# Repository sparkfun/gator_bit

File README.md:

SparkFun gator:bit v2
========================================

[*SparkFun gator:bit v2 (15162)*](https://www.sparkfun.com/products/15162)

The SparkFun gator:bit is an all-in-one prototyping platform for the micro:bit. Each pin is accessible by alligator clip, eliminating the need for breadboard or jumper wires.

Repository Contents
------------------
* **/Firmware** - Example code used with gator:bit. While they are compiled HEX codes, you can modify the example code once they are imported into MakeCode editor.
* **/Hardware** - Eagle design files (.brd, .sch)
* **/Production** - Production panel files (.brd)

Documentation
--------------
* **[Hookup Guide](https://learn.sparkfun.com/tutorials/sparkfun-gatorbit-v20-hookup-guide)** - Basic hookup guide for the gator:bit v2.

Versions
--------------
* **[v1](https://github.com/sparkfun/gator_bit/tree/v10)** - Version 1, Initial Release
* **[v2](https://github.com/sparkfun/gator_bit/)** - Version 2, Updated power handling, output pins now reach a proper voltage.

License Information
-------------------

This product is _**open source**_! 

Please review the LICENSE.md file for license information. 

If you have any questions or concerns on licensing, please contact techsupport@sparkfun.com.

Distributed as-is; no warranty is given.

- Your friends at SparkFun.

_<COLLABORATION CREDIT>_

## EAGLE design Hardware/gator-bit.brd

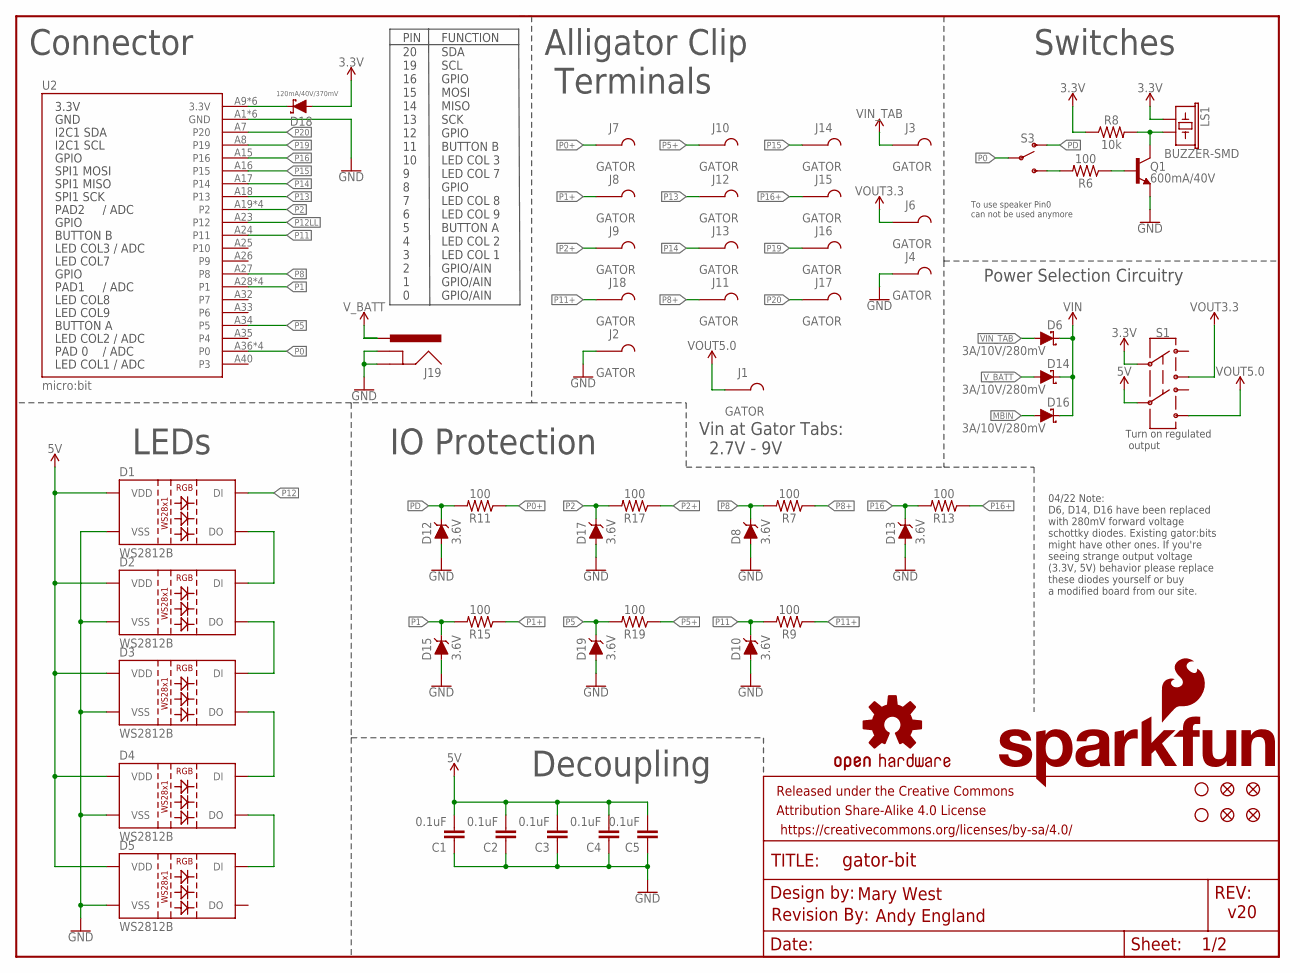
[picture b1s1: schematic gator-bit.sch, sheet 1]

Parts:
C1, C2, C3, C4, C5: 0.1uF; 0603
D1, D2, D3, D4, D5: WS2812B
D6, D14, D16: 3A/10V/280mV; SOD-323
D8, D10, D12, D13, D15, D17, D19: 3.6V; SOD-323
D18: 120mA/40V/370mV; SOD-523
FD1, FD2, FD3, FD4: FIDUCIAL1X2; FIDUCIAL-1X2
FRAME1: FRAME-LETTER; CREATIVE_COMMONS
H1, H2: STAND-OFF
J1, J2, J3, J4, J6, J7, J8, J9, J10, J11, J12, J13, J14, J15, J16, J17, J18: GATOR
J19: POWER_JACKPTH_LOCK; POWER_JACK_PTH_LOCK
LOGO1: SFE_LOGO_NAME_FLAME.3_INCH; SFE_LOGO_NAME_FLAME_.3
LOGO2: OSHW-LOGOM; OSHW-LOGO-M
LOGO3: REVISION
LS1: BUZZER-SMD; BUZZER-CCV
Q1: 600mA/40V; SOT23-3
R6, R7, R9, R11, R13, R15, R17, R19: 100; 0603
R8: 10k; 0603
S1: SWITCH-DPDT-SMD-AYZ0202; SWITCH_DPDT_SMD_AYZ0202
S3: SWITCH-SPDT-SMD-AYZ0202; SWITCH_DPDT_SMD_AYZ0202
U2: micro:bit; MICRO:BIT_RA_PTH

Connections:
3.3V: D18.A, LS1.+ (1), R8.1, S1.2; also elsewhere on the board
5V: C1.2, C2.2, C3.2, C4.2, C5.2, D1.1 (VDD), D2.1 (VDD), D3.1 (VDD), D4.1 (VDD), D5.1 (VDD), S1.5; also elsewhere on the board
GND: C1.1, C2.1, C3.1, C4.1, C5.1, D1.3 (VSS), D2.3 (VSS), D3.3 (VSS), D4.3 (VSS), D5.3 (VSS), D8.A, D10.A, D12.A, D13.A, D15.A, D17.A, D19.A, J2.P$1, J2.P$2, J4.P$1, J4.P$2, J19.GND, J19.GNDBREAK, Q1.2 (E), U2.A1 (GND), U2.A2 (GND), U2.A3 (GND), U2.A4 (GND), U2.A5 (GND), U2.A6 (GND); also elsewhere on the board
MBIN: D16.A, D18.C, U2.A9 (3.3V), U2.A10 (3.3V), U2.A11 (3.3V), U2.A12 (3.3V), U2.A13 (3.3V), U2.A14 (3.3V)
unnamed: LS1.- (2), Q1.3 (C), R8.2
unnamed: D1.2 (DO), D2.4 (DI)
unnamed: D2.2 (DO), D3.4 (DI)
unnamed: D3.2 (DO), D4.4 (DI)
unnamed: D4.2 (DO), D5.4 (DI)
unnamed: R6.2, S3.3 (S)
unnamed: Q1.1 (B), R6.1
P0: S3.2, U2.A36 (P0), U2.A37 (P0), U2.A38 (P0), U2.A39 (P0)
P0+: J7.P$1, J7.P$2, R11.1
P1: D15.C, R15.2, U2.A28 (P1), U2.A29 (P1), U2.A30 (P1), U2.A31 (P1)
P1+: J8.P$1, J8.P$2, R15.1
P2: D17.C, R17.2, U2.A19 (P2), U2.A20 (P2), U2.A21 (P2), U2.A22 (P2)
P2+: J9.P$1, J9.P$2, R17.1
P5: D19.C, R19.2, U2.A34 (P5)
P5+: J10.P$1, J10.P$2, R19.1
P8: D8.C, R7.2, U2.A27 (P8)
P8+: J11.P$1, J11.P$2, R7.1
P11: D10.C, R9.2, U2.A24 (P11)
P11+: J18.P$1, J18.P$2, R9.1
P12: D1.4 (DI); also elsewhere on the board
P12LL: U2.A23 (P12); also elsewhere on the board
P13: J12.P$1, J12.P$2, U2.A18 (P13)
P14: J13.P$1, J13.P$2, U2.A17 (P14)
P15: J14.P$1, J14.P$2, U2.A16 (P15)
P16: D13.C, R13.2, U2.A15 (P16)
P16+: J15.P$1, J15.P$2, R13.1
P19: J16.P$1, J16.P$2, U2.A8 (P19)
P20: J17.P$1, J17.P$2, U2.A7 (P20)
PD: D12.C, R11.2, S3.1 (O)
VIN: D6.C, D14.C, D16.C; also elsewhere on the board
VIN_TAB: D6.A, J3.P$1, J3.P$2
VOUT3.3: J6.P$1, J6.P$2, S1.3; also elsewhere on the board
VOUT5.0: J1.P$1, J1.P$2, S1.6; also elsewhere on the board
V_BATT: D14.A, J19.PWR

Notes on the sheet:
v20
Connector
20 19 16 15 14 13 12 11 10 9 8 7 6 5 4 3 2 1 0
SDA SCL GPIO MOSI MISO SCK GPIO BUTTON B LED COL 3 LED COL 7 GPIO LED COL 8 LED COL 9 BUTTON A LED COL 2 LED COL 1 GPIO/AIN GPIO/AIN GPIO/AIN
PIN
FUNCTION
Mary West
Alligator Clip Terminals
Switches
LEDs
Decoupling
IO Protection
To use speaker Pin0 can not be used anymore
Power Selection Circuitry
Turn on regulated output
Vin at Gator Tabs: 2.7V - 9V
Andy England
04/22 Note: D6, D14, D16 have been replaced with 280mV forward voltage schottky diodes. Existing gator:bits might have other ones. If you're seeing strange output voltage (3.3V, 5V) behavior please replace these diodes yourself or buy a modified board from our site.

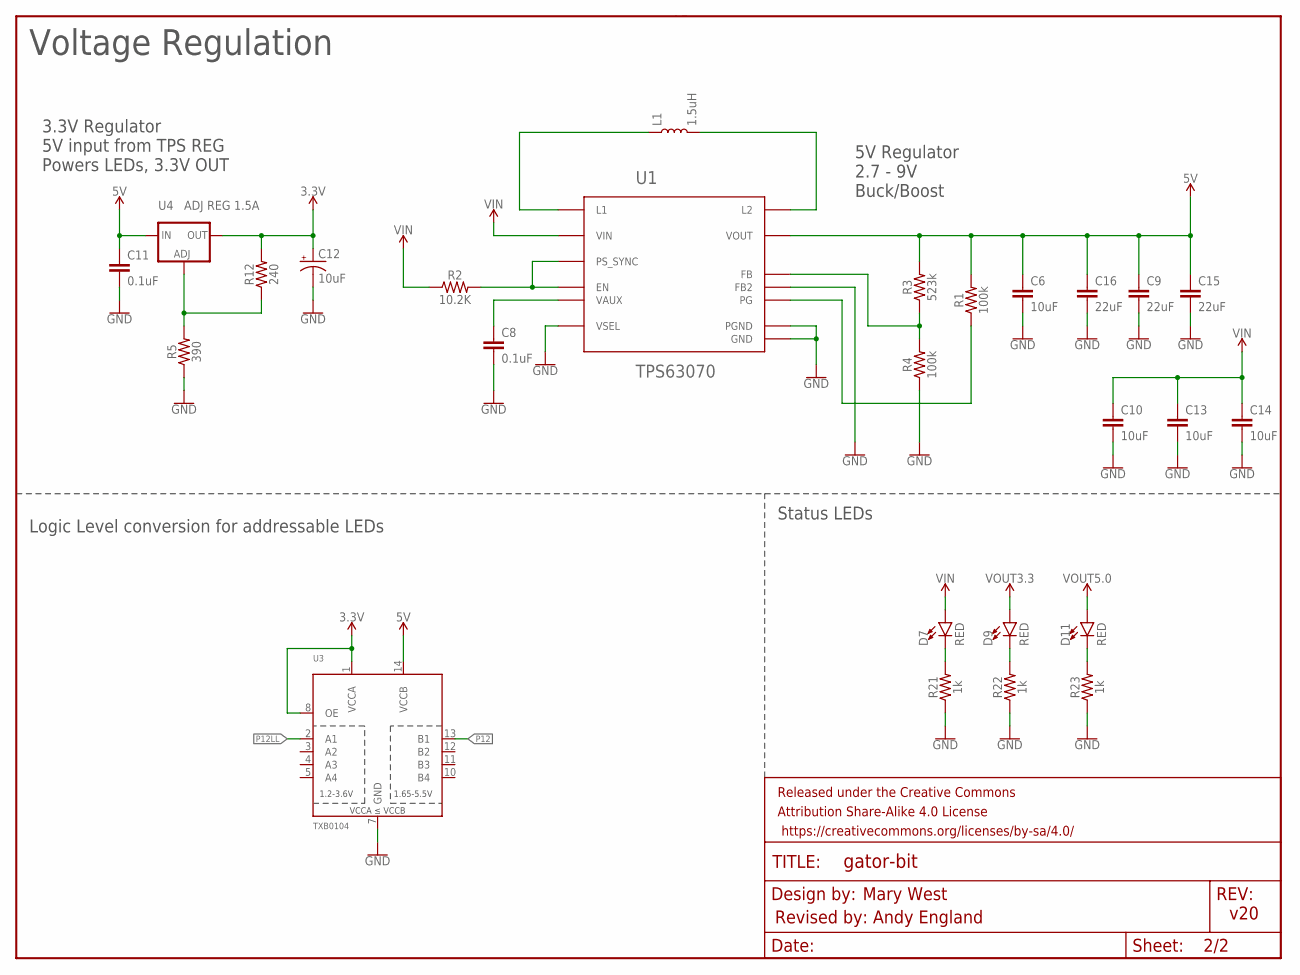
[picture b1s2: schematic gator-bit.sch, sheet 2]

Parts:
C6, C14: 10uF; 0603
C8, C11: 0.1uF; 0603
C9, C15, C16: 22uF; 0805
C10, C13: 10uF; 0805
C12: 10uF; EIA3216
D7, D9, D11: RED; LED-0603
FRAME3: FRAME-LETTER; CREATIVE_COMMONS
L1: 1.5uH; XFL4020
R1, R4: 100k; 0603
R2: 10.2K; 0603
R3: 523k; 0603
R5: 390; 0603
R12: 240; 0603
R21, R22, R23: 1k; 0603
U1: TPS63070; TPS63070RNM
U3: TXB0104; TSSOP14
U4: ADJ REG 1.5A; SOT223

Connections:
3.3V: C12.+, R12.2, U3.1 (VCCA), U3.8 (OE), U4.2 (OUT), U4.4 (OUT); also elsewhere on the board
5V: C6.1, C9.1, C11.1, C15.1, C16.1, R1.2, R3.2, U1.P$7 (VOUT), U3.14 (VCCB), U4.3 (IN); also elsewhere on the board
GND: C6.2, C8.2, C9.2, C10.2, C11.2, C12.-, C13.2, C14.2, C15.2, C16.2, R4.1, R5.1, R21.1, R22.1, R23.1, U1.P$4 (GND), U1.P$6 (FB2), U1.P$10 (PGND), U1.P$15 (VSEL), U3.7 (GND); also elsewhere on the board
unnamed: L1.P$1 (1), U1.P$11 (L1)
unnamed: L1.P$2 (2), U1.P$9 (L2)
unnamed: D7.C, R21.2
unnamed: R3.1, R4.2, U1.P$5 (FB)
unnamed: C8.1, U1.P$3 (VAUX)
unnamed: R2.2, U1.P$1 (PS_SYNC), U1.P$14 (EN)
unnamed: R1.1, U1.P$2 (PG)
unnamed: R5.2, R12.1, U4.1 (ADJ)
unnamed: D9.C, R22.2
unnamed: D11.C, R23.2
P12: U3.13 (B1); also elsewhere on the board
P12LL: U3.2 (A1); also elsewhere on the board
VIN: C10.1, C13.1, C14.1, D7.A, R2.1, U1.P$12 (VIN); also elsewhere on the board
VOUT3.3: D9.A; also elsewhere on the board
VOUT5.0: D11.A; also elsewhere on the board

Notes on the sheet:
Voltage Regulation
Mary West
v20
5V Regulator 2.7 - 9V Buck/Boost
3.3V Regulator 5V input from TPS REG Powers LEDs, 3.3V OUT
Logic Level conversion for addressable LEDs
Status LEDs
Revised by: Andy England

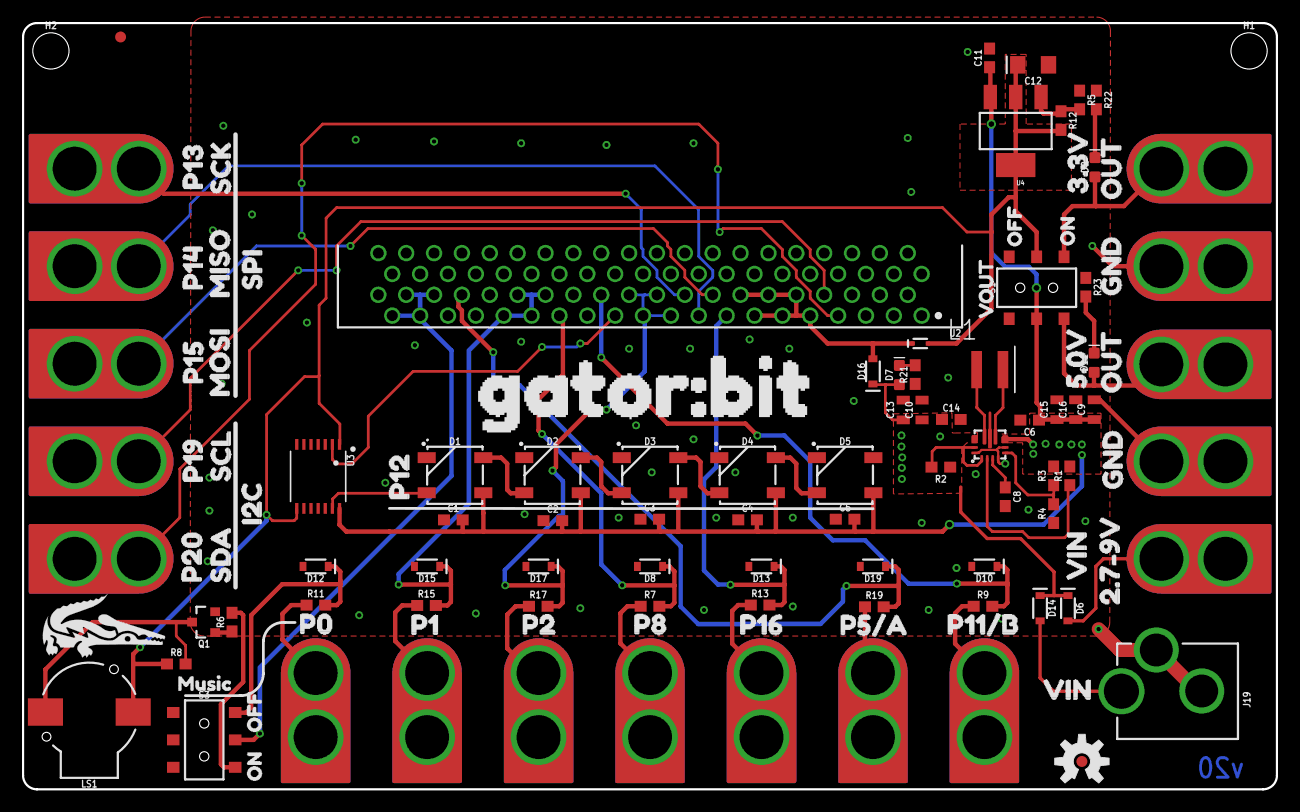
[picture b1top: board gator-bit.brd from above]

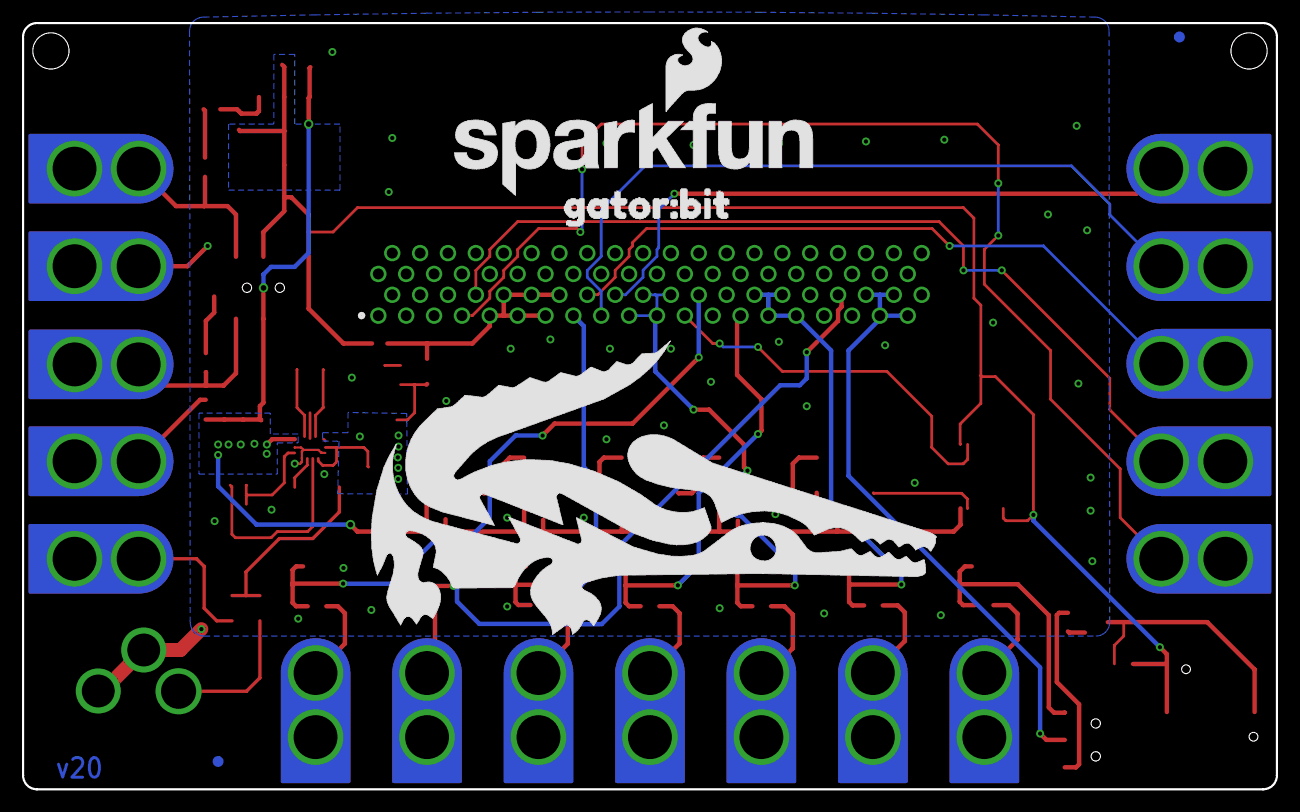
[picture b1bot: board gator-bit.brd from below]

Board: 2 copper layers, 114.3 x 69.8 mm, 128 parts (4 on the bottom side), 48 nets.

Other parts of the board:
U$1: 2#7#9V21
U$2: 3#3V25
U$3: 5#0V23
U$4: ORDERING_INSTRUCTIONS
U$5: GATOR#BIT26
U$6: GATOR#BIT32
U$7, U$8: GND22
U$9: I2C7
U$10: MISO5
U$11: MOSI4
U$12: MUSIC28
U$13, U$36: OFF29
U$14, U$37: ON30
U$15, U$16: OUT24
U$17: P5#A18
U$18: P11#B19
U$19: P013
U$20: P114
U$21: P130
U$22: P199
U$23: P208
U$24: P215
U$25: P816
U$26: P1227
U$27: P1411
U$28: P1510
U$29: P1617
U$30: SCK1
U$31: SCL2
U$32: SDA3
U$33: SPI6
U$34, U$39: VIN20
U$35: VOUT31

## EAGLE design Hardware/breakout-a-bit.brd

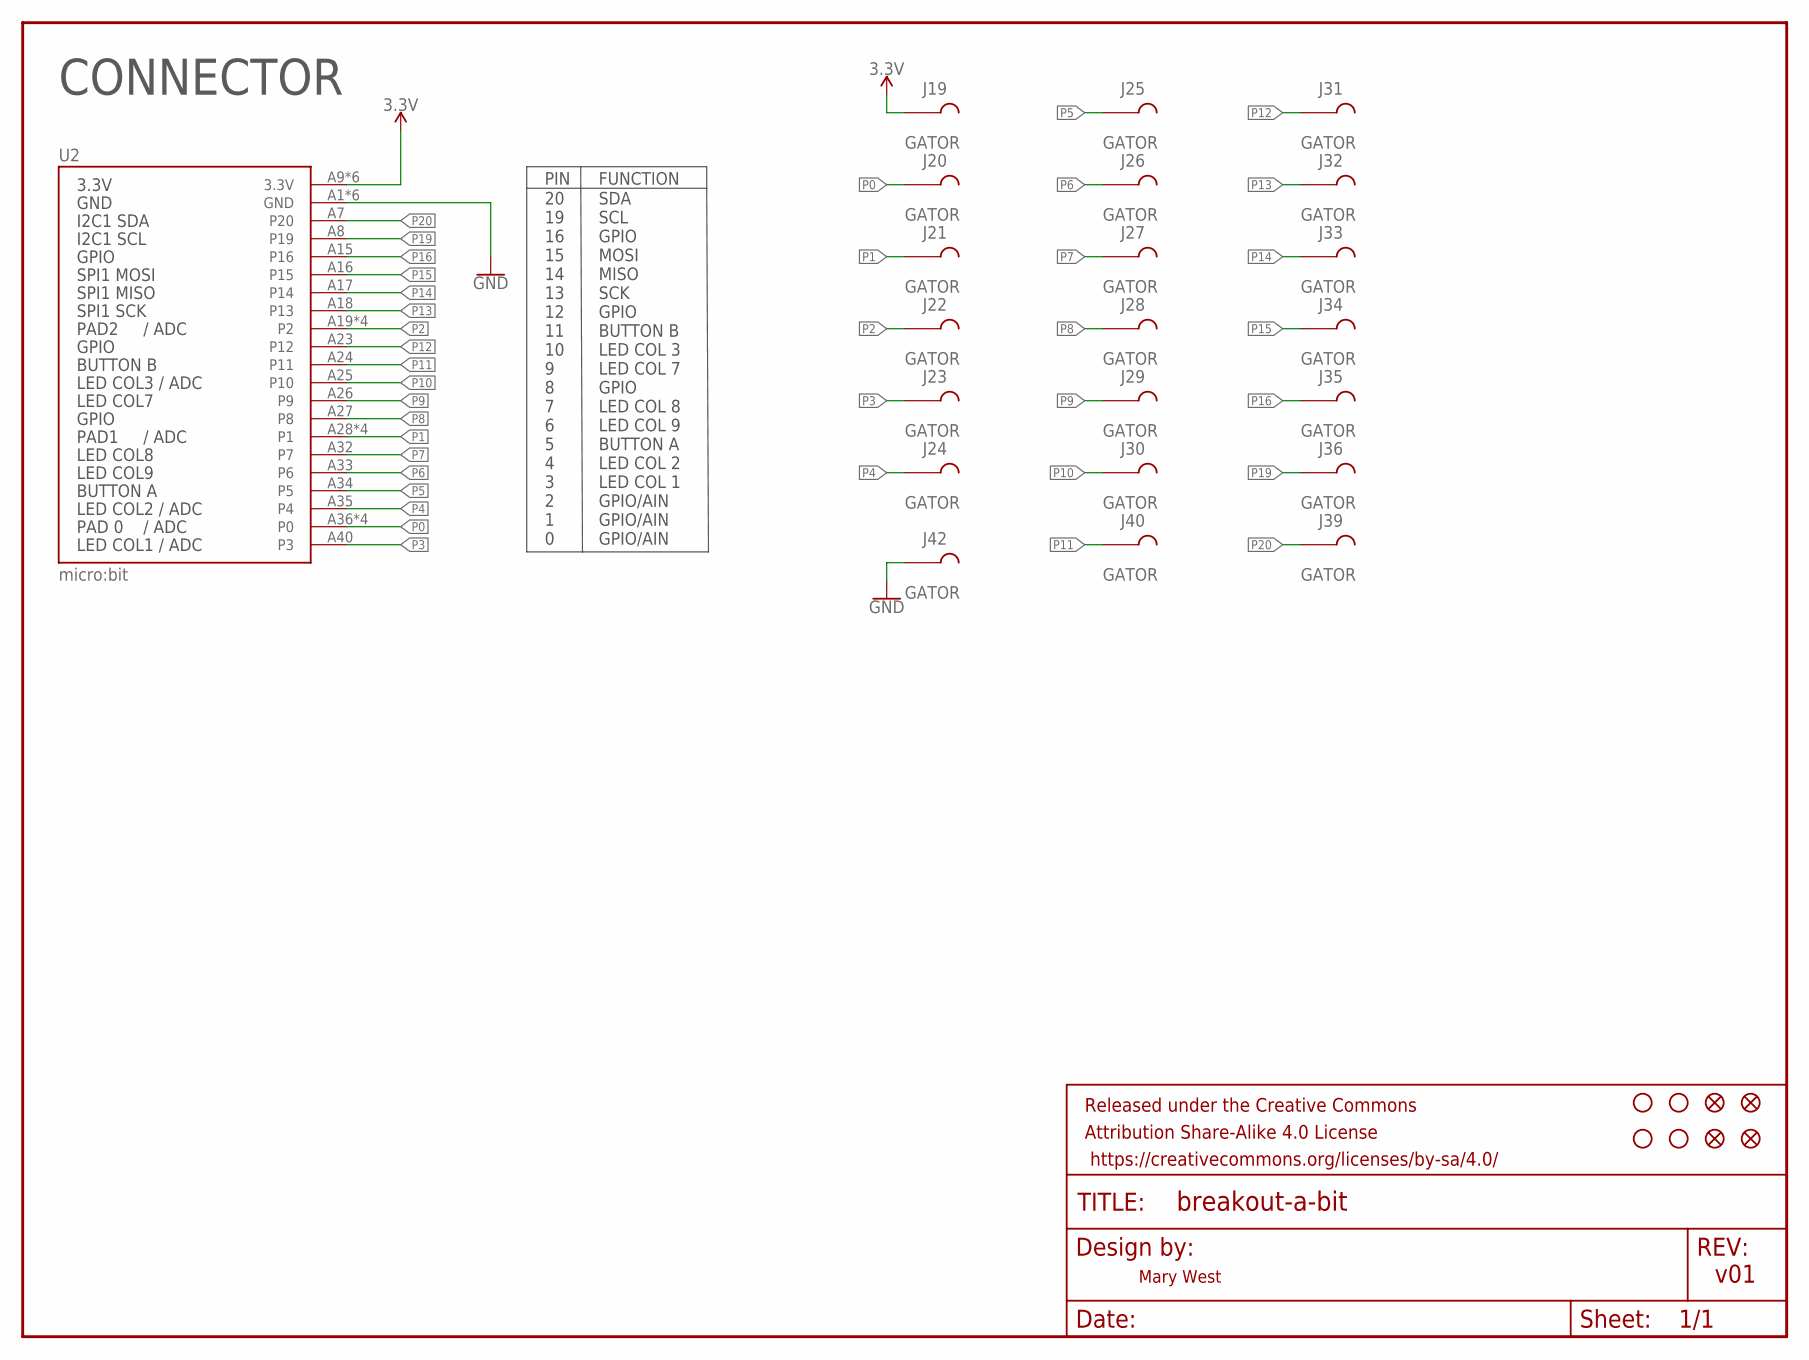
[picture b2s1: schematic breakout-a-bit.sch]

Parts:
FD1, FD2, FD3, FD4: FIDUCIAL1X2; FIDUCIAL-1X2
FRAME1: FRAME-LETTER; CREATIVE_COMMONS
H1, H2, H3, H4: STAND-OFF
J19, J20, J21, J22, J23, J24, J25, J26, J27, J28, J29, J30, J31, J32, J33, J34, J35, J36, J39, J40, J42: GATOR
U2: micro:bit; MICRO:BIT_RA_PTH

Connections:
3.3V: J19.P$1, U2.A9 (3.3V), U2.A10 (3.3V), U2.A11 (3.3V), U2.A12 (3.3V), U2.A13 (3.3V), U2.A14 (3.3V)
GND: J42.P$1, U2.A1 (GND), U2.A2 (GND), U2.A3 (GND), U2.A4 (GND), U2.A5 (GND), U2.A6 (GND)
P0: J20.P$1, U2.A36 (P0), U2.A37 (P0), U2.A38 (P0), U2.A39 (P0)
P1: J21.P$1, U2.A28 (P1), U2.A29 (P1), U2.A30 (P1), U2.A31 (P1)
P2: J22.P$1, U2.A19 (P2), U2.A20 (P2), U2.A21 (P2), U2.A22 (P2)
P3: J23.P$1, U2.A40 (P3)
P4: J24.P$1, U2.A35 (P4)
P5: J25.P$1, U2.A34 (P5)
P6: J26.P$1, U2.A33 (P6)
P7: J27.P$1, U2.A32 (P7)
P8: J28.P$1, U2.A27 (P8)
P9: J29.P$1, U2.A26 (P9)
P10: J30.P$1, U2.A25 (P10)
P11: J40.P$1, U2.A24 (P11)
P12: J31.P$1, U2.A23 (P12)
P13: J32.P$1, U2.A18 (P13)
P14: J33.P$1, U2.A17 (P14)
P15: J34.P$1, U2.A16 (P15)
P16: J35.P$1, U2.A15 (P16)
P19: J36.P$1, U2.A8 (P19)
P20: J39.P$1, U2.A7 (P20)

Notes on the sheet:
v01
CONNECTOR
20 19 16 15 14 13 12 11 10 9 8 7 6 5 4 3 2 1 0
SDA SCL GPIO MOSI MISO SCK GPIO BUTTON B LED COL 3 LED COL 7 GPIO LED COL 8 LED COL 9 BUTTON A LED COL 2 LED COL 1 GPIO/AIN GPIO/AIN GPIO/AIN
PIN
FUNCTION
Mary West

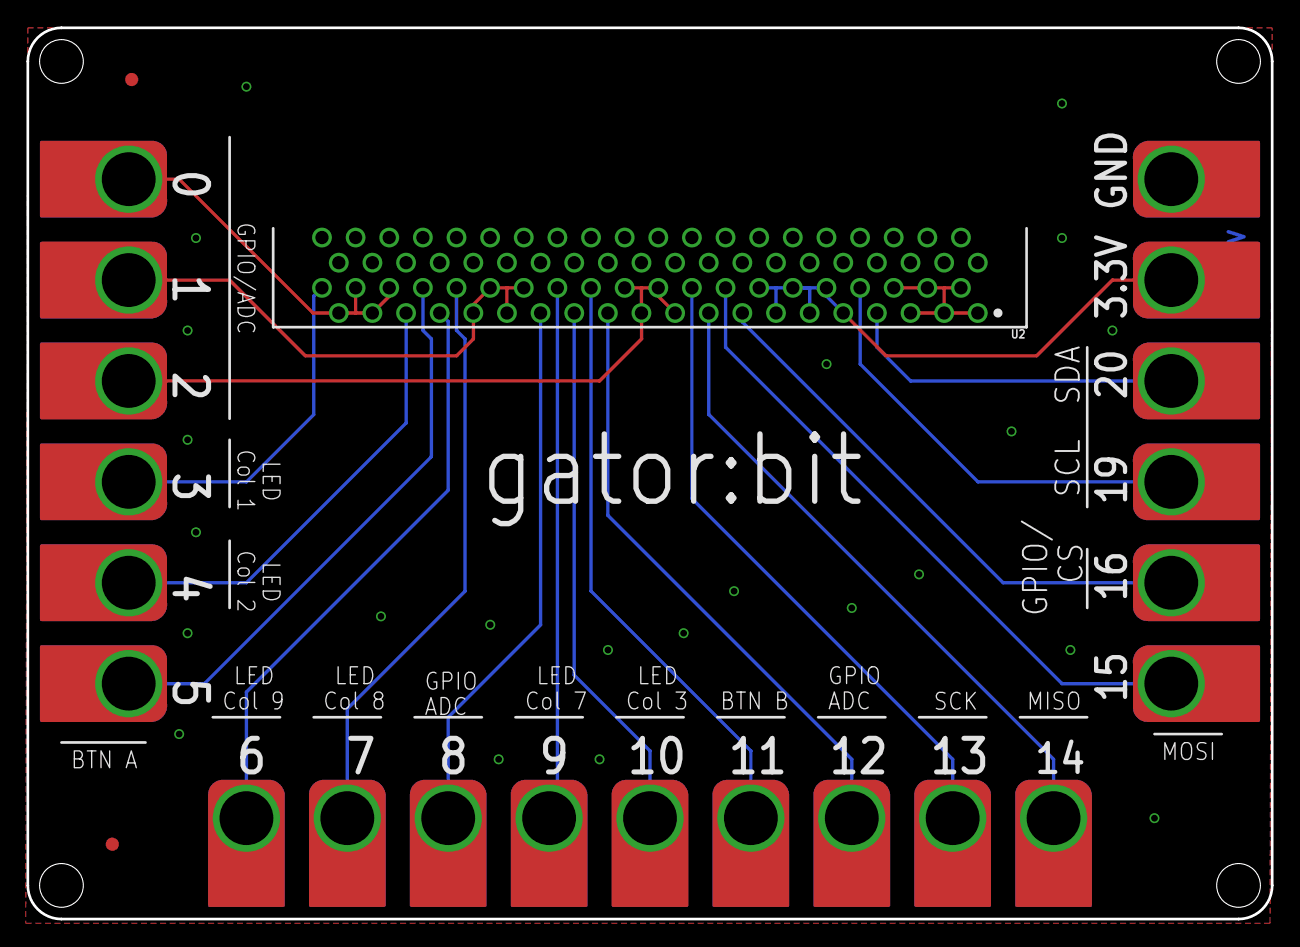
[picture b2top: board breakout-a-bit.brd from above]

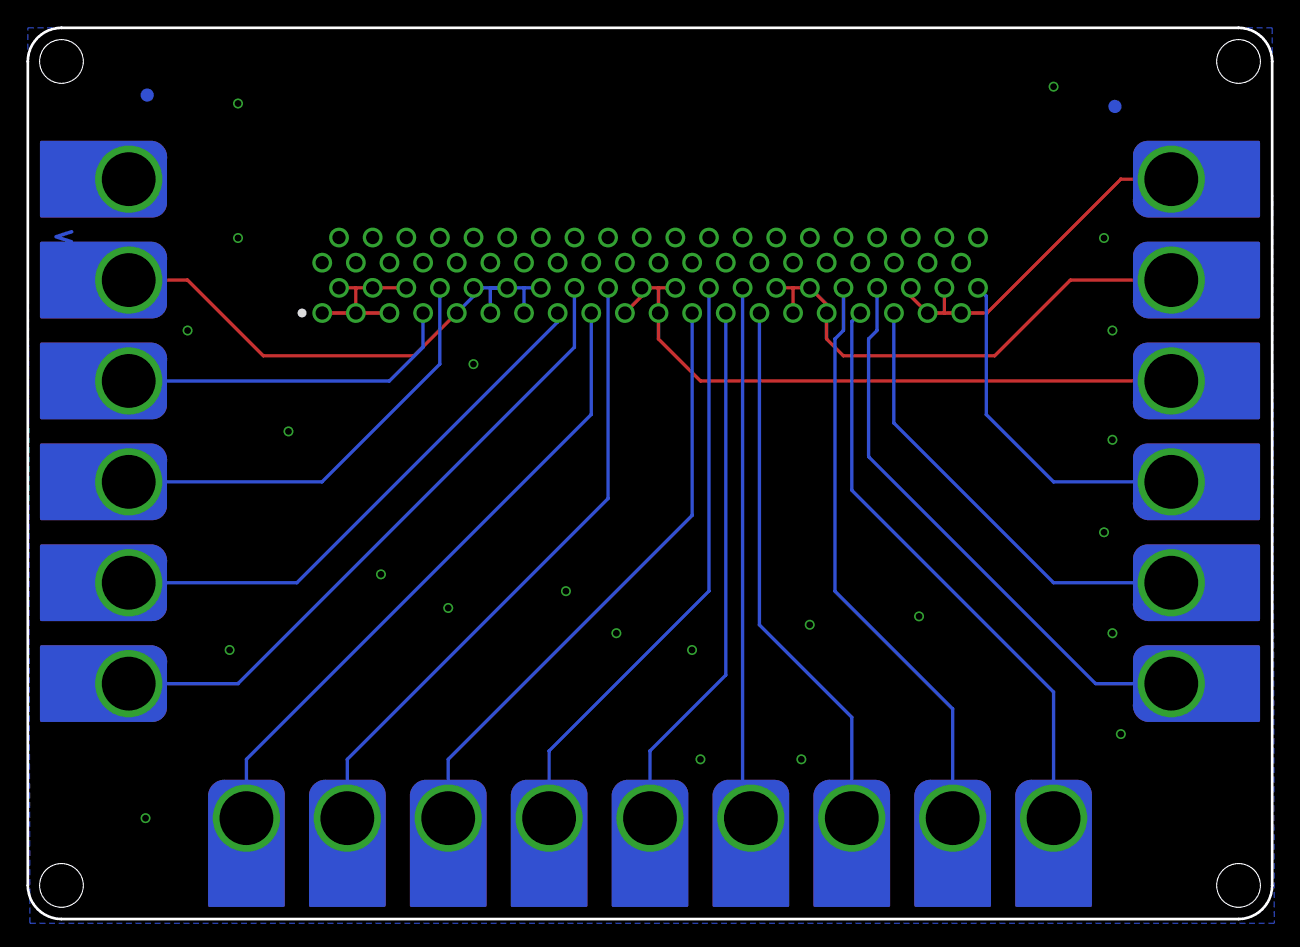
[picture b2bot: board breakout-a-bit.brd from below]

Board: 2 copper layers, 94.0 x 67.3 mm, 32 parts (2 on the bottom side), 21 nets.

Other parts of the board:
U$4: ORDERING_INSTRUCTIONS

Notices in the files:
parts and their libraries:
SparkFun-Aesthetics: Licensing: Creative Commons ShareAlike 4.0 International - https://creativecommons.org/licenses/by-sa/4.0
SparkFun-Aesthetics: Released under the Creative Commons Attribution Share-Alike 4.0 License
SparkFun-Aesthetics: https://creativecommons.org/licenses/by-sa/4.0
